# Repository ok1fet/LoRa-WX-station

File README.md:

<h1>LoRa-APRS-WX-station</h1>
<p>Záměrem bylo vytvořit jednoduchou malou meteosondu. Aby byla levná, aby ji bylo možné bez obav na kopci přidělat na strom :)</p>
<ul>
<p>Informace ze sondy mají sloužit pro piloty paraglidingu, které zajímá hlavně směr a rychlost větru. Proto byla programu věnována značná pozornost. Měření probíhá každých 20 sekund a data se agregují po 5 minutách. Navíc se spočítá průměrná hodnota větru a vyhodnotí se maximální nárazy větru. Směr větru se měří <a href="https://en.wikipedia.org/wiki/Yamartino_method">Yamartino metodou.</a></p>
</ul>  
<p>Data se ukládají na cloudové uložiště na serveru www.aprs.fi.</p>
<p>Pro měření rychlosti a směru větru jsou použita čidla k meteostanici WH1080, která jsou na našem trhu dostupná jako náhradní díly za rozumný peníz.</p>
</p>

<p>Meteorologická stanice <a href="http://cukrak.wz.cz/"> Cukrák.</a> Zdrojová data na www.aprs.fi/ok1fet-4.</a></p>
<p>Meteorologická stanice <a href="http://jevinka.wz.cz/"> Jeviněves.</a> Zdrojová data na www.aprs.fi/ok1fet-5.</a></p>
<p>Meteorologická stanice <a href="http://revnicov.wz.cz/"> Řevničov.</a> Zdrojová data na www.aprs.fi/ok1fet-14.</a></p>
<p> Moxon antena na 433MHz. <a href="https://www.thingiverse.com/thing:2068392/files">Zdrojová data</a> pro 3D printer na Thingiverse.</a></p>

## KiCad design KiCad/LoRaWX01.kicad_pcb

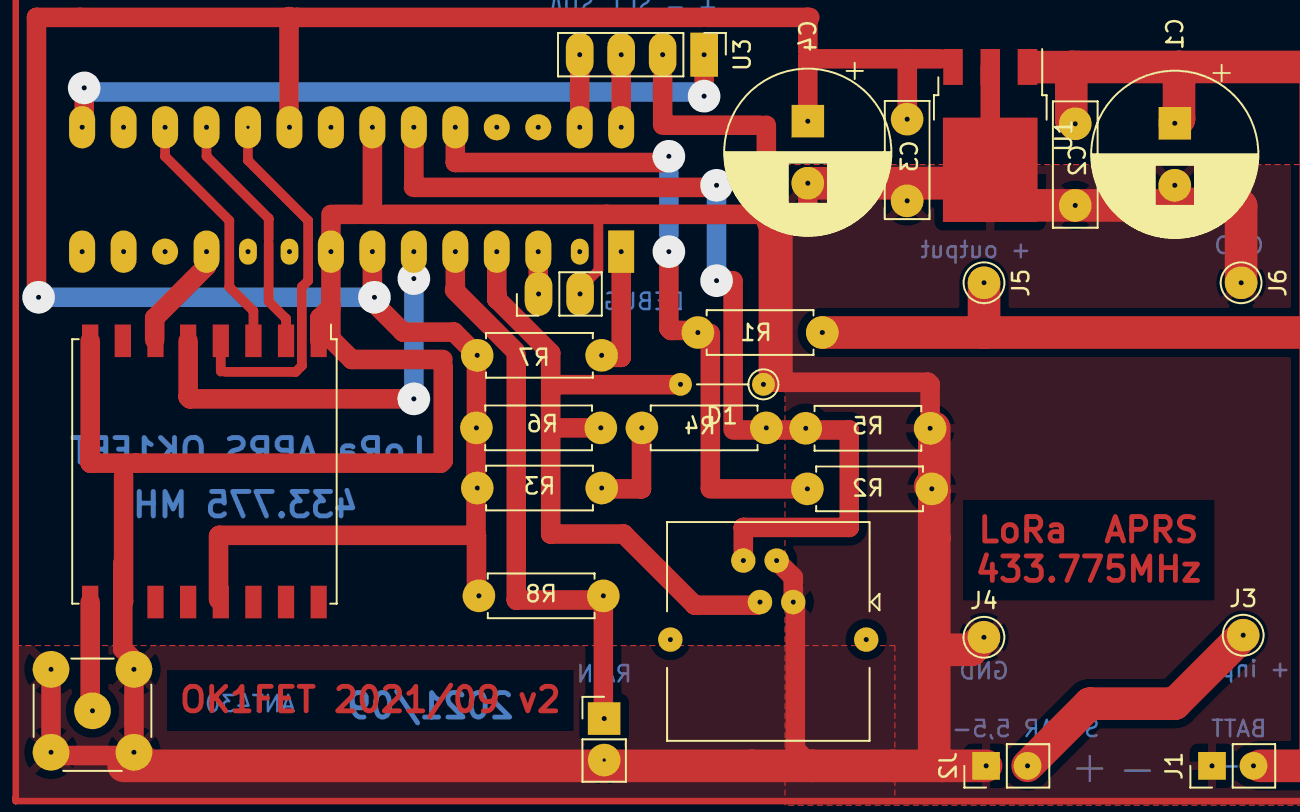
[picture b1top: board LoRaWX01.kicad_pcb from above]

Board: 2 copper layers, 27 parts (1 on the bottom side), 20 nets.

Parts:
C1: 500uF; CP_Radial_D10.0mm_P3.80mm
C2: M1; C_Disc_D7.5mm_W2.5mm_P5.00mm
C3: M1; C_Disc_D7.0mm_W2.5mm_P5.00mm
C4: 50uF; CP_Radial_D10.0mm_P3.80mm
D1: LED; R_Axial_DIN0204_L3.6mm_D1.6mm_P5.08mm_Vertical
J1: BATT; PinHeader_1x02_P2.54mm_Vertical
J2: SOLAR 5,5-6V; PinHeader_1x02_P2.54mm_Vertical
J3: + input; Pin_D1.0mm_L10.0mm
J4, J6: GND; Pin_D1.0mm_L10.0mm
J5: + output; Pin_D1.0mm_L10.0mm
J7: W_SONDA; RJ14_Connfly_DS1133-S4_Horizontal
J8: ANT-433; SMA_Molex_73251-2200_Horizontal
J10: DEBUG; PinHeader_1x02_P2.54mm_Vertical
J11: RAIN; PinHeader_1x02_P2.54mm_Vertical
R1: 91K18; R_Axial_DIN0207_L6.3mm_D2.5mm_P7.62mm_Horizontal
R2: 10K09; R_Axial_DIN0207_L6.3mm_D2.5mm_P7.62mm_Horizontal
R3, R4, R5, R6, R7, R8: 10K; R_Axial_DIN0207_L6.3mm_D2.5mm_P7.62mm_Horizontal
U1: LF33_TO252; TO-252-3_TabPin2
U2: ATmega328-PU; DIP-28_W7.62mm
U3: BME280; PinHeader_1x04_P2.54mm_Vertical
U4: RFM96W-315S2; HOPERF_RFM9XW_SMD

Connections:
GND: C1.2, C2.2, C3.2, C4.2, D1.1 (K), J1.1, J2.1, J4.1, J6.1, J7.1, J7.2, J8.2, J10.2, J11.2, R2.2, R5.2, U1.2 (GND), U2.8 (GND), U2.22 (GND), U3.2 (GND), U4.1 (GND), U4.8 (GND), U4.10 (GND)
unnamed: C1.1, C2.1, J1.2, J5.1, R1.1, U1.1 (VI)
unnamed: C3.1, C4.1, R3.1, R6.1, R7.1, R8.1, U1.3 (VO), U2.7 (VCC), U2.20 (AVCC), U4.13 (3.3V)
unnamed: D1.2 (A), J7.3, R6.2, U2.4 (PD2)
unnamed: J2.2, J3.1
unnamed: J7.4, R4.2, R5.1, U2.23 (PC0)
unnamed: J8.1, U4.9 (ANT)
unnamed: J10.1, U2.3 (PD1)
unnamed: J11.1, R8.2, U2.5 (PD3)
unnamed: R1.2, R2.1, U2.24 (PC1)
unnamed: R3.2, R4.1
unnamed: R7.2, U2.1 (~RESET~/PC6)
unnamed: U2.6 (PD4), U4.5 (NSS)
unnamed: U2.11 (PD5), U4.6 (RESET)
unnamed: U2.15 (PB1), U3.1 (VDD)
unnamed: U2.17 (PB3), U4.3 (MOSI)
unnamed: U2.18 (PB4), U4.2 (MISO)
unnamed: U2.19 (PB5), U4.4 (SCK)
unnamed: U2.27 (PC4), U3.4 (SDA)
unnamed: U2.28 (PC5), U3.3 (SCL)

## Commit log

2021-05-01 Create LoRa_TX_WX_ATMEGA328_V2
2022-01-10 zmeny v napajeni bme280
2022-01-10 zmeny v napajeni
